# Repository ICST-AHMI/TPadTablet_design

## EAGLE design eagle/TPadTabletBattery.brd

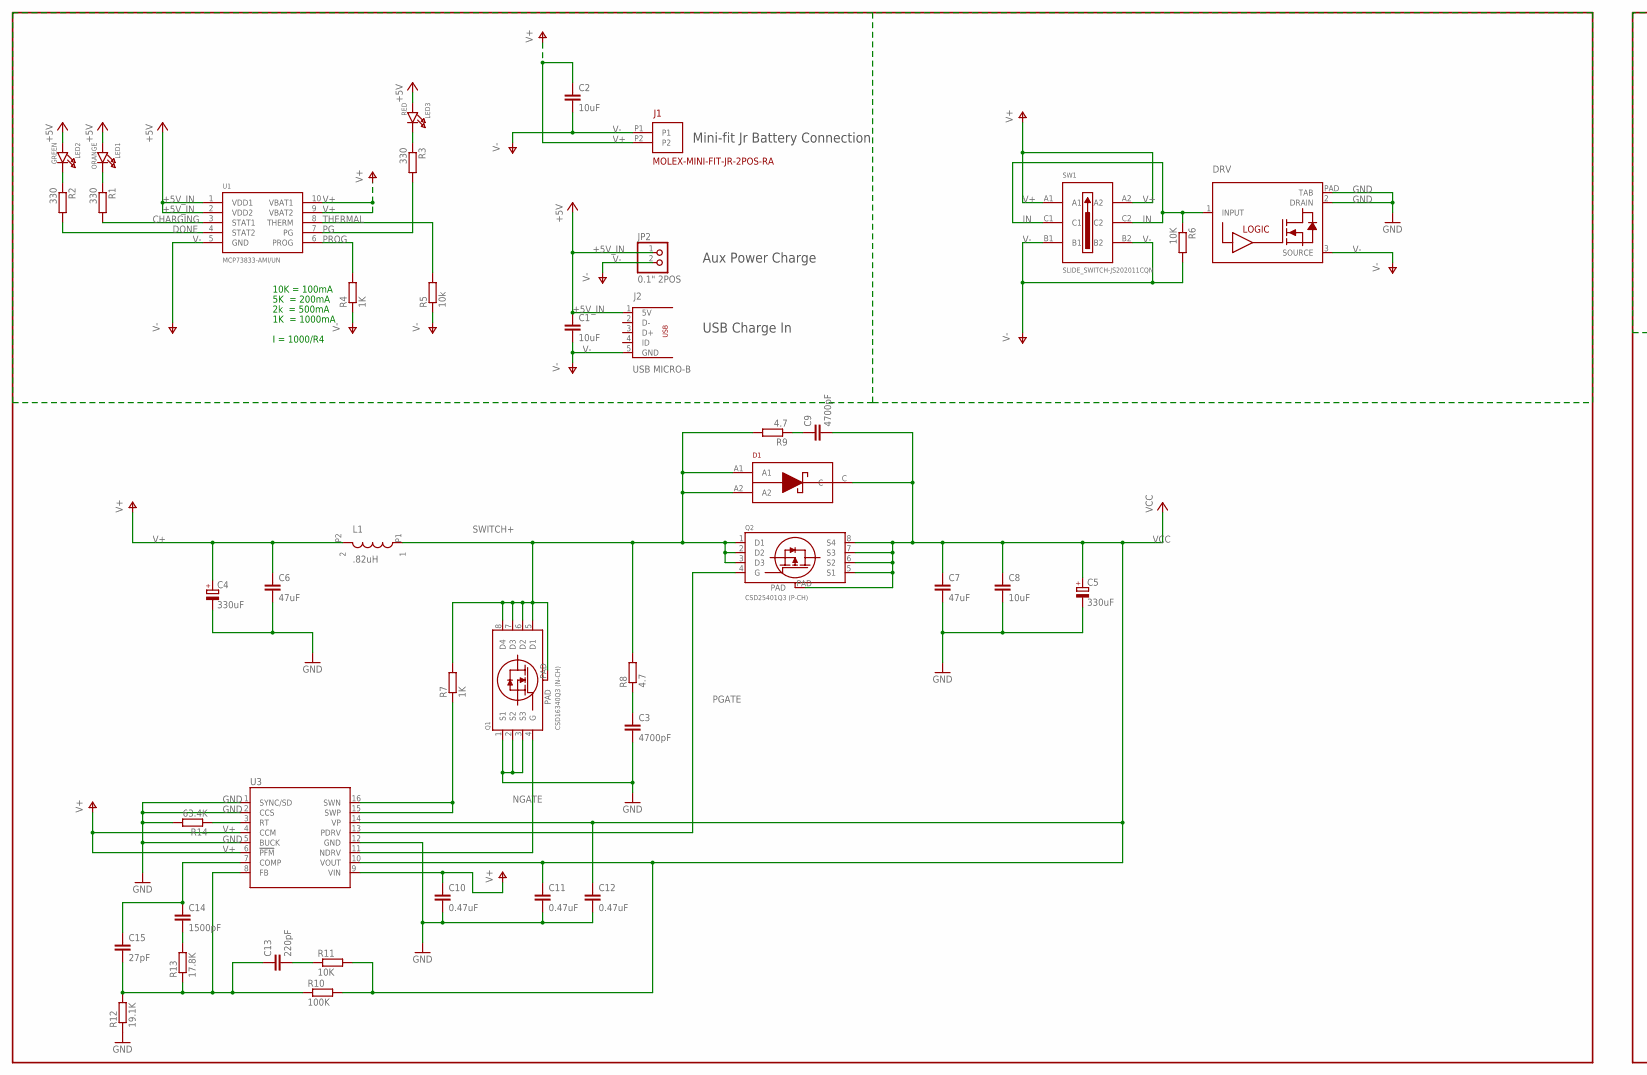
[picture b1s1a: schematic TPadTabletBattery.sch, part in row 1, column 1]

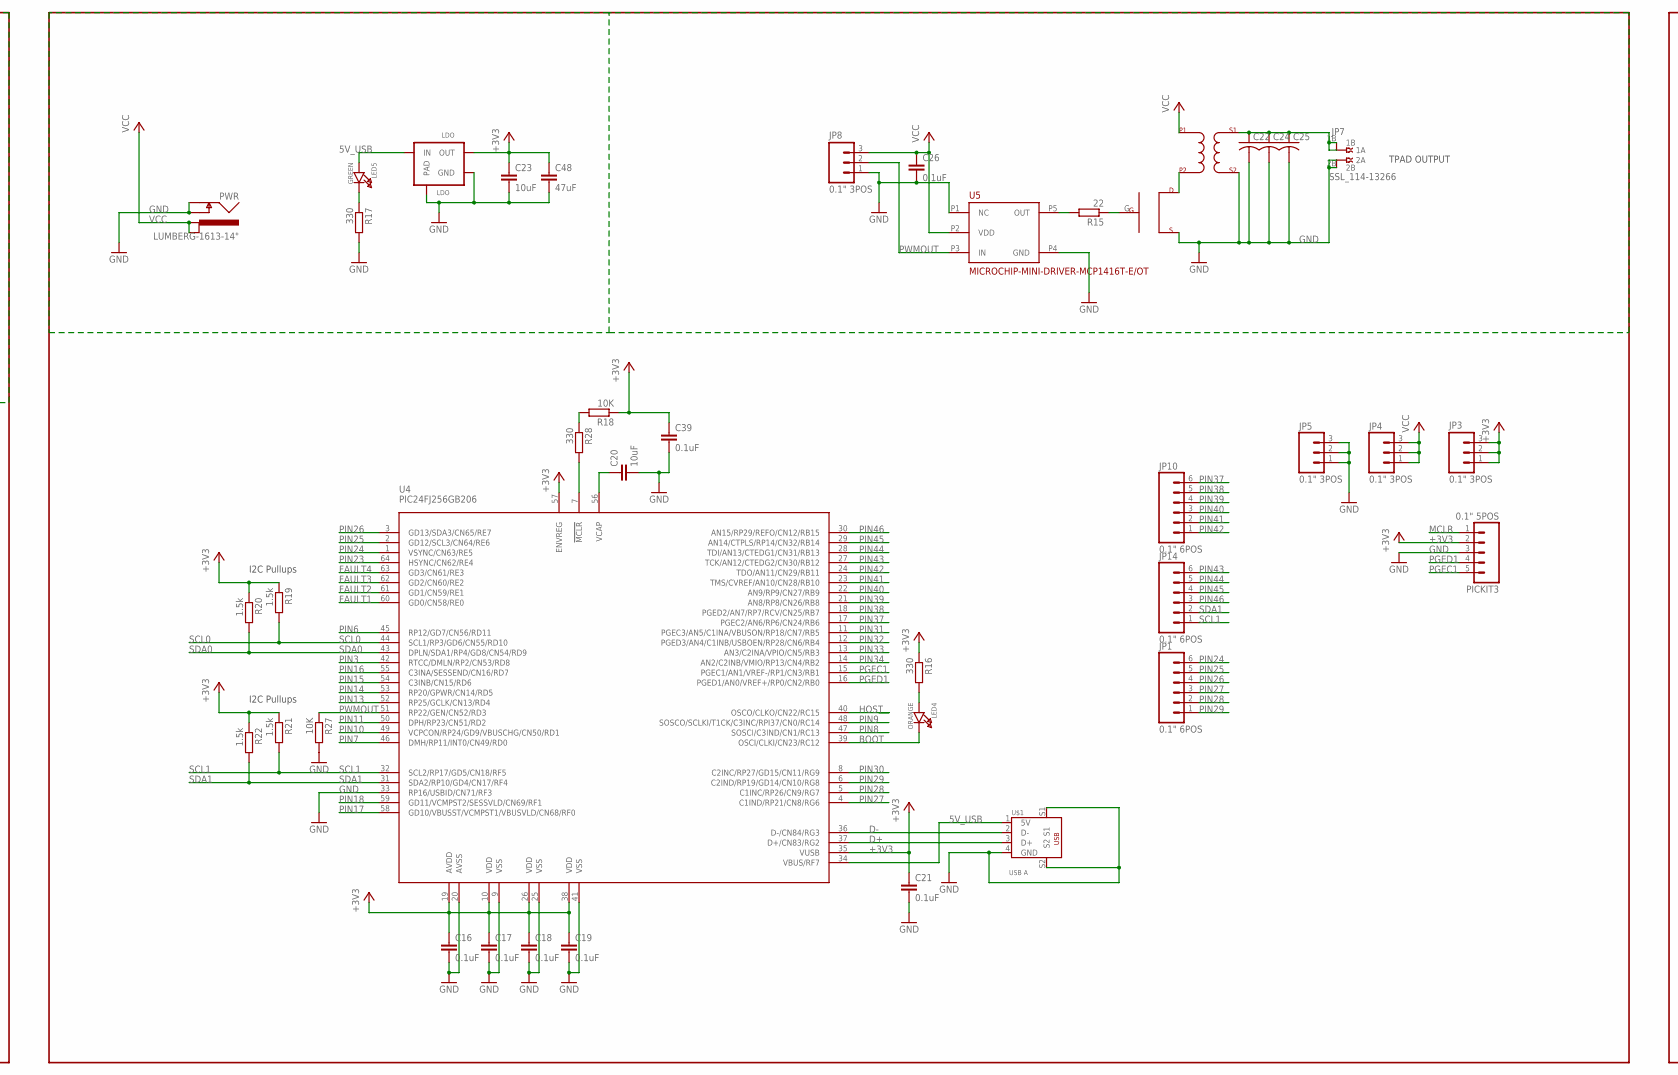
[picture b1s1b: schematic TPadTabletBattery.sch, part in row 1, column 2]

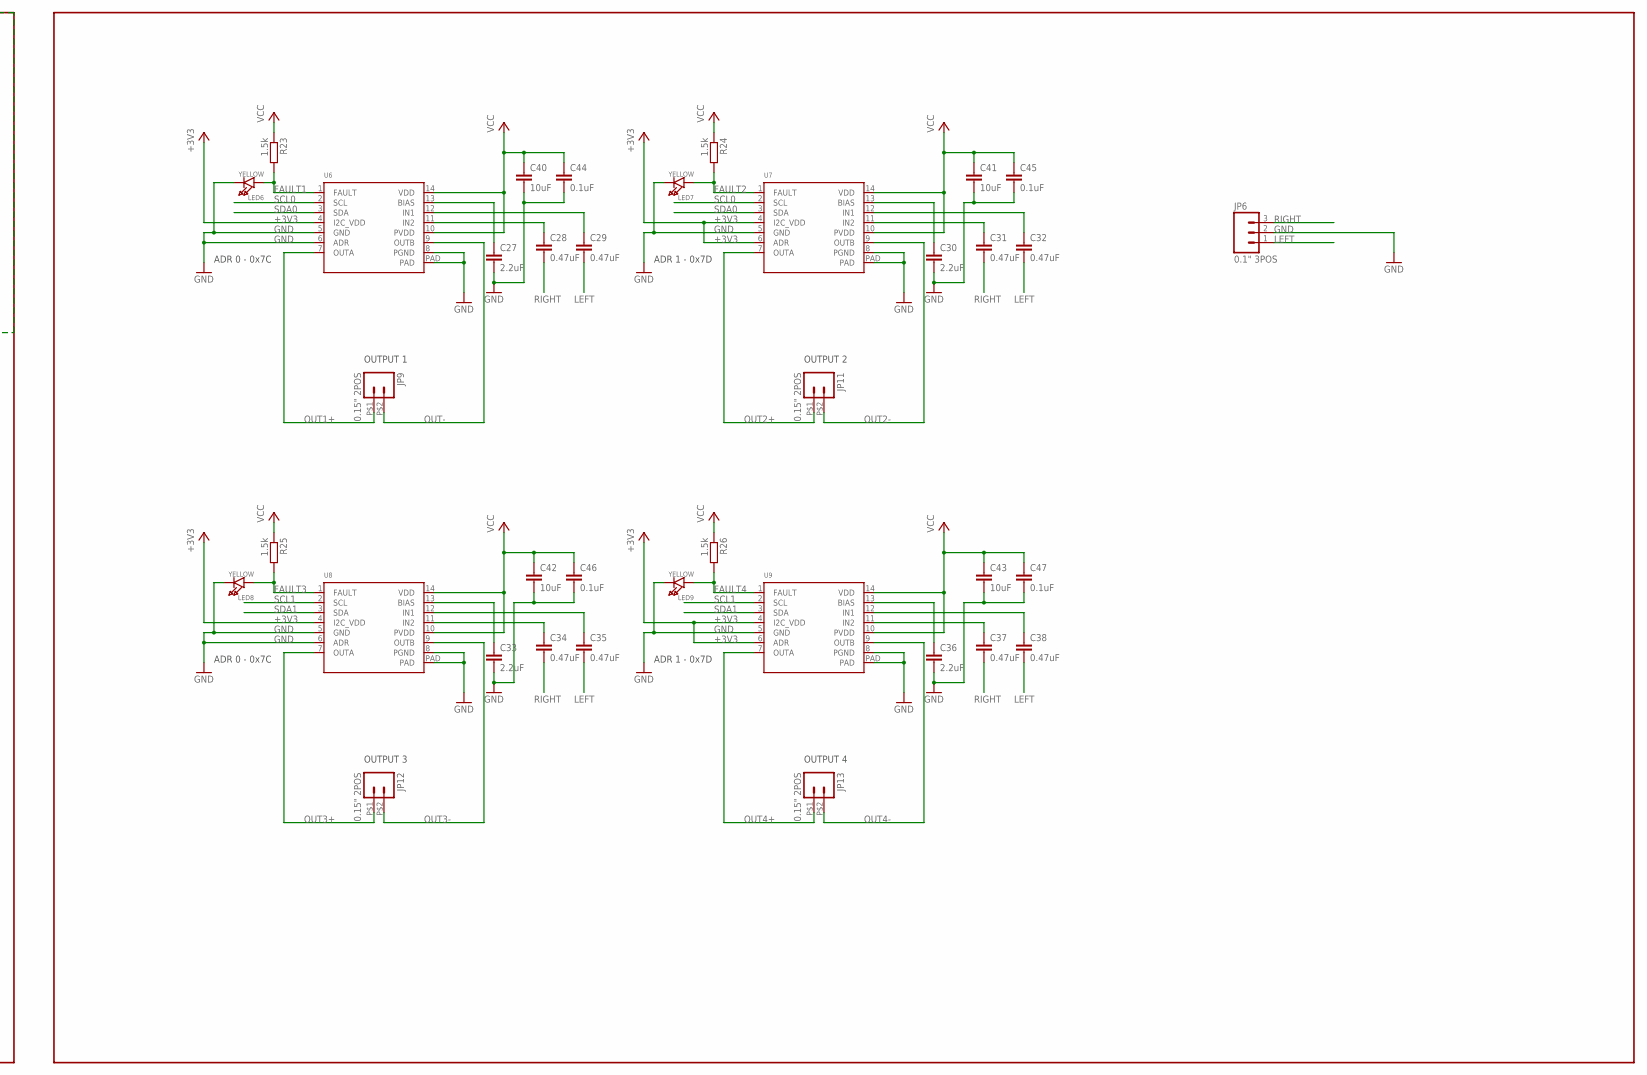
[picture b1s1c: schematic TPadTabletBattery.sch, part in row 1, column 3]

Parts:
C1, C2, C8, C20, C23, C40, C41, C42, C43: 10uF; C0805
C3, C9: 4700pF; C0603
C4, C5: 330uF; C/6032-28R
C6, C7, C48: 47uF; C1210
C10, C11, C12, C28, C29, C31, C32, C34, C35, C37, C38: 0.47uF; C0603
C13: 220pF; C0603
C14: 1500pF; C0603
C15: 27pF; C0603
C16, C17, C18, C19, C21, C26, C39, C44, C45, C46, C47: 0.1uF; C0603
C22, C24, C25: C-US050-035X075; C050-035X075
C27, C30, C33, C36: 2.2uF; C0603
D1: POWER-DIODE_PDS835L
DRV: VLN5050; SOT-223
J1: MOLEX-MINI-FIT-JR-2POS-RA
J2: USB MICRO-B; USB-MICROB_SMD
JP1, JP10, JP14: 0.1" 6POS; 1X06
JP2: 0.1" 2POS; MICROBUILDER_1X02_ROUND
JP3, JP4, JP5, JP6, JP8: 0.1" 3POS; 1X03
JP7: SSL_114-13266
JP9, JP11, JP12, JP13: 0.15" 2POS; 1X02_BIG
L1: .82uH; .82UH_INDUCTOR-IHLP3232DZERR82M01
LDO: LDO; SOT-223
LED1, LED4: ORANGE; MICROBUILDER_CHIPLED_0603
LED2, LED5: GREEN; MICROBUILDER_CHIPLED_0603
LED3: RED; MICROBUILDER_CHIPLED_0603
LED6, LED7, LED8, LED9: YELLOW; MICROBUILDER_CHIPLED_0603
PICKIT3: 0.1" 5POS; 1X05
PWR: LUMBERG-1613-14"; LUMBERG-1613_14
Q1: CSD16340Q3; CSDXXXXQ3
Q2: CSD25401Q3; CSDXXXXQ3
Q3: STP27N3LH5; TPAD_TO220
R1, R2, R3, R16, R17, R28: 330; R0603
R4: 1K; R0805
R5: 10k; R0805
R6, R11, R18, R27: 10K; R0603
R7: 1K; R0603
R8, R9: 4.7; R0603
R10: 100K; R0603
R12: 19.1K; R0603
R13: 17.8K; R0603
R14: 63.4K; R0603
R15: 22; R0603
R19, R20, R21, R22, R23, R24, R25, R26: 1.5k; R0603
SW1: SLIDE_SWITCH-JS202011CQN
U1: MCP73833-AMI/UN; MICROBUILDER_MSOP10
U3: TPS43000; TSSOP16
U4: PIC24FJ256GB206; PIC24FXXX_TQFP64
U5: MICROCHIP-MINI-DRIVER-MCP1416T-E/OT
U6, U7, U8, U9: LM48100Q; LM48100
U$1: USB A; USB-A_SOCKET-THT
U$4: TRANSFORMER

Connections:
5V_USB: LDO.1 (IN), LED5.A, U4.34 (VBUS/RF7), U$1.1 (5V)
+3V3: C16.1, C17.1, C18.1, C19.1, C21.1, C23.1, C39.1, C48.1, JP3.1, JP3.2, JP3.3, LDO.3 (OUT), PICKIT3.2, R16.1, R18.1, R19.1, R20.1, R21.1, R22.1, U4.10 (VDD), U4.19 (AVDD), U4.26 (VDD), U4.35 (VUSB), U4.38 (VDD), U4.57 (ENVREG), U6.4 (I2C_VDD), U7.4 (I2C_VDD), U7.6 (ADR), U8.4 (I2C_VDD), U9.4 (I2C_VDD), U9.6 (ADR)
+5V_IN: C1.1, J2.1 (5V), JP2.1, LED1.A, LED2.A, LED3.A, U1.1 (VDD1), U1.2 (VDD2)
BOOT: LED4.C, U4.39 (OSCI/CLKI/CN23/RC12)
CHARGING: R1.2, U1.3 (STAT1)
D+: U4.37 (D+/CN83/RG2), U$1.3 (D+)
D-: U4.36 (D-/CN84/RG3), U$1.2 (D-)
DONE: R2.2, U1.4 (STAT2)
FAULT1: LED6.A, R23.2, U4.60 (GD0/CN58/RE0), U6.1 (FAULT)
FAULT2: LED7.A, R24.2, U4.61 (GD1/CN59/RE1), U7.1 (FAULT)
FAULT3: LED8.A, R25.2, U4.62 (GD2/CN60/RE2), U8.1 (FAULT)
FAULT4: LED9.A, R26.2, U4.63 (GD3/CN61/RE3), U9.1 (FAULT)
GND: C3.2, C4.-, C5.-, C6.2, C7.2, C8.2, C10.2, C11.2, C12.2, C16.2, C17.2, C18.2, C19.2, C20.2, C21.2, C22.2, C23.2, C24.2, C25.2, C26.2, C27.2, C30.2, C33.2, C36.2, C39.2, C40.2, C41.2, C42.2, C43.2, C44.2, C45.2, C46.2, C47.2, C48.2, DRV.2 (DRAIN), DRV.PAD (TAB), JP5.1, JP5.2, JP5.3, JP6.2, JP7.2A, JP7.2B, JP8.1, LDO.2 (GND), LDO.PAD, LED6.C, LED7.C, LED8.C, LED9.C, PICKIT3.3, PWR.1 (GND), PWR.2 (GND_INS), Q1.1 (S1), Q1.2 (S2), Q1.3 (S3), Q3.S, R12.1, R14.2, R17.2, R27.2, U3.1 (SYNC/SD), U3.2 (CCS), U3.5 (BUCK), U3.12 (GND), U4.9 (VSS), U4.20 (AVSS), U4.25 (VSS), U4.33 (RP16/USBID/CN71/RF3), U4.41 (VSS), U5.P1 (NC), U5.P4 (GND), U6.5 (GND), U6.6 (ADR), U6.8 (PGND), U6.PAD, U7.5 (GND), U7.8 (PGND), U7.PAD, U8.5 (GND), U8.6 (ADR), U8.8 (PGND), U8.PAD, U9.5 (GND), U9.8 (PGND), U9.PAD, U$1.4 (GND), U$1.S1, U$1.S2, U$4.S2
HOST: U4.40 (OSCO/CLKO/CN22/RC15)
IN: DRV.1 (INPUT), R6.1, SW1.C1, SW1.C2
LEFT: C29.2, C32.2, C35.2, C38.2, JP6.1
MCLR: PICKIT3.1, R18.2, R28.1
unnamed: R7.1, U3.15 (SWP), U3.16 (SWN)
unnamed: LED2.C, R2.1
unnamed: LED1.C, R1.1
unnamed: LED3.C, R3.1
unnamed: R28.2, U4.7 (!MCLR)
unnamed: C9.1, R9.1
unnamed: C13.1, C15.2, R10.1, R12.2, R13.1, U3.8 (FB)
unnamed: C14.1, C15.1, U3.7 (COMP)
unnamed: C3.1, R8.1
unnamed: C20.1, U4.56 (VCAP)
unnamed: R14.1, U3.3 (RT)
unnamed: C14.2, R13.2
unnamed: LED4.A, R16.2
unnamed: C13.2, R11.1
unnamed: Q3.D, U$4.P2
unnamed: R15.2, U5.P5 (OUT)
unnamed: C22.1, C24.1, C25.1, JP7.1A, JP7.1B, U$4.S1
unnamed: LED5.C, R17.1
unnamed: Q3.G, R15.1
unnamed: C27.1, U6.13 (BIAS)
unnamed: C29.1, U6.12 (IN1)
unnamed: C28.1, U6.11 (IN2)
unnamed: C30.1, U7.13 (BIAS)
unnamed: C32.1, U7.12 (IN1)
unnamed: C31.1, U7.11 (IN2)
unnamed: C33.1, U8.13 (BIAS)
unnamed: C35.1, U8.12 (IN1)
unnamed: C34.1, U8.11 (IN2)
unnamed: C36.1, U9.13 (BIAS)
unnamed: C38.1, U9.12 (IN1)
unnamed: C37.1, U9.11 (IN2)
NGATE: Q1.4 (G), U3.11 (NDRV)
OUT1+: JP9.P$1 (1), U6.7 (OUTA)
OUT2+: JP11.P$1 (1), U7.7 (OUTA)
OUT2-: JP11.P$2 (2), U7.9 (OUTB)
OUT3+: JP12.P$1 (1), U8.7 (OUTA)
OUT3-: JP12.P$2 (2), U8.9 (OUTB)
OUT4+: JP13.P$1 (1), U9.7 (OUTA)
OUT4-: JP13.P$2 (2), U9.9 (OUTB)
OUT-: JP9.P$2 (2), U6.9 (OUTB)
PG: R3.2, U1.7 (PG)
PGATE: Q2.4 (G), U3.13 (PDRV)
PGEC1: PICKIT3.5, U4.15 (PGEC1/AN1/VREF-/RP1/CN3/RB1)
PGED1: PICKIT3.4, U4.16 (PGED1/AN0/VREF+/RP0/CN2/RB0)
PIN3: U4.42 (RTCC/DMLN/RP2/CN53/RD8)
PIN6: U4.45 (RP12/GD7/CN56/RD11)
PIN7: U4.46 (DMH/RP11/INT0/CN49/RD0)
PIN8: U4.47 (SOSCI/C3IND/CN1/RC13)
PIN9: U4.48 (SOSCO/SCLKI/T1CK/C3INC/RPI37/CN0/RC14)
PIN10: U4.49 (VCPCON/RP24/GD9/VBUSCHG/CN50/RD1)
PIN11: U4.50 (DPH/RP23/CN51/RD2)
PIN13: U4.52 (RP25/GCLK/CN13/RD4)
PIN14: U4.53 (RP20/GPWR/CN14/RD5)
PIN15: U4.54 (C3INB/CN15/RD6)
PIN16: U4.55 (C3INA/SESSEND/CN16/RD7)
PIN17: U4.58 (GD10/VBUSST/VCMPST1/VBUSVLD/CN68/RF0)
PIN18: U4.59 (GD11/VCMPST2/SESSVLD/CN69/RF1)
PIN23: U4.64 (HSYNC/CN62/RE4)
PIN24: JP1.6, U4.1 (VSYNC/CN63/RE5)
PIN25: JP1.5, U4.2 (GD12/SCL3/CN64/RE6)
PIN26: JP1.4, U4.3 (GD13/SDA3/CN65/RE7)
PIN27: JP1.3, U4.4 (C1IND/RP21/CN8/RG6)
PIN28: JP1.2, U4.5 (C1INC/RP26/CN9/RG7)
PIN29: JP1.1, U4.6 (C2IND/RP19/GD14/CN10/RG8)
PIN30: U4.8 (C2INC/RP27/GD15/CN11/RG9)
PIN31: U4.11 (PGEC3/AN5/C1INA/VBUSON/RP18/CN7/RB5)
PIN32: U4.12 (PGED3/AN4/C1INB/USBOEN/RP28/CN6/RB4)
PIN33: U4.13 (AN3/C2INA/VPIO/CN5/RB3)
PIN34: U4.14 (AN2/C2INB/VMIO/RP13/CN4/RB2)
PIN37: JP10.6, U4.17 (PGEC2/AN6/RP6/CN24/RB6)
PIN38: JP10.5, U4.18 (PGED2/AN7/RP7/RCV/CN25/RB7)
PIN39: JP10.4, U4.21 (AN8/RP8/CN26/RB8)
PIN40: JP10.3, U4.22 (AN9/RP9/CN27/RB9)
PIN41: JP10.2, U4.23 (TMS/CVREF/AN10/CN28/RB10)
PIN42: JP10.1, U4.24 (TDO/AN11/CN29/RB11)
PIN43: JP14.6, U4.27 (TCK/AN12/CTEDG2/CN30/RB12)
PIN44: JP14.5, U4.28 (TDI/AN13/CTEDG1/CN31/RB13)
PIN45: JP14.4, U4.29 (AN14/CTPLS/RP14/CN32/RB14)
PIN46: JP14.3, U4.30 (AN15/RP29/REFO/CN12/RB15)
PROG: R4.2, U1.6 (PROG)
PWMOUT: JP8.2, R27.1, U4.51 (RP22/GEN/CN52/RD3), U5.P3 (IN)
RIGHT: C28.2, C31.2, C34.2, C37.2, JP6.3
SCL0: R19.2, U4.44 (SCL1/RP3/GD6/CN55/RD10), U6.2 (SCL), U7.2 (SCL)
SCL1: JP14.1, R21.2, U4.32 (SCL2/RP17/GD5/CN18/RF5), U8.2 (SCL), U9.2 (SCL)
SDA0: R20.2, U4.43 (DPLN/SDA1/RP4/GD8/CN54/RD9), U6.3 (SDA), U7.3 (SDA)
SDA1: JP14.2, R22.2, U4.31 (SDA2/RP10/GD4/CN17/RF4), U8.3 (SDA), U9.3 (SDA)
SWITCH+: D1.A1, D1.A2, L1.P1 (1), Q1.5 (D1), Q1.6 (D2), Q1.7 (D3), Q1.8 (D4), Q1.PAD, Q2.1 (D1), Q2.2 (D2), Q2.3 (D3), R7.2, R8.2, R9.2
THERMAL: R5.2, U1.8 (THERM)
V+: C2.1, C4.+, C6.1, C10.1, J1.P2, L1.P2 (2), SW1.A1, SW1.A2, U1.9 (VBAT2), U1.10 (VBAT1), U3.4 (CCM), U3.6 (!PFM), U3.9 (VIN)
V-: C1.2, C2.2, DRV.3 (SOURCE), J1.P1, J2.5 (GND), JP2.2, R4.1, R5.1, R6.2, SW1.B1, SW1.B2, U1.5 (GND)
VCC: C5.+, C7.1, C8.1, C9.2, C11.1, C12.1, C26.1, C40.1, C41.1, C42.1, C43.1, C44.1, C45.1, C46.1, C47.1, D1.C, JP4.1, JP4.2, JP4.3, JP8.3, PWR.3 (PWR_1), PWR.4 (PWR_2), Q2.5 (S1), Q2.6 (S2), Q2.7 (S3), Q2.8 (S4), Q2.PAD, R10.2, R11.2, R23.1, R24.1, R25.1, R26.1, U3.10 (VOUT), U3.14 (VP), U5.P2 (VDD), U6.10 (PVDD), U6.14 (VDD), U7.10 (PVDD), U7.14 (VDD), U8.10 (PVDD), U8.14 (VDD), U9.10 (PVDD), U9.14 (VDD), U$4.P1

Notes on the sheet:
10K = 100mA
5K = 200mA
2k = 500mA
1K = 1000mA
I = 1000/R4
Mini-fit Jr Battery Connection
USB Charge In
Aux Power Charge
ADR 0 - 0x7C
I2C Pullups
OUTPUT 1
TPAD OUTPUT
OUTPUT 2
ADR 1 - 0x7D
OUTPUT 3
OUTPUT 4

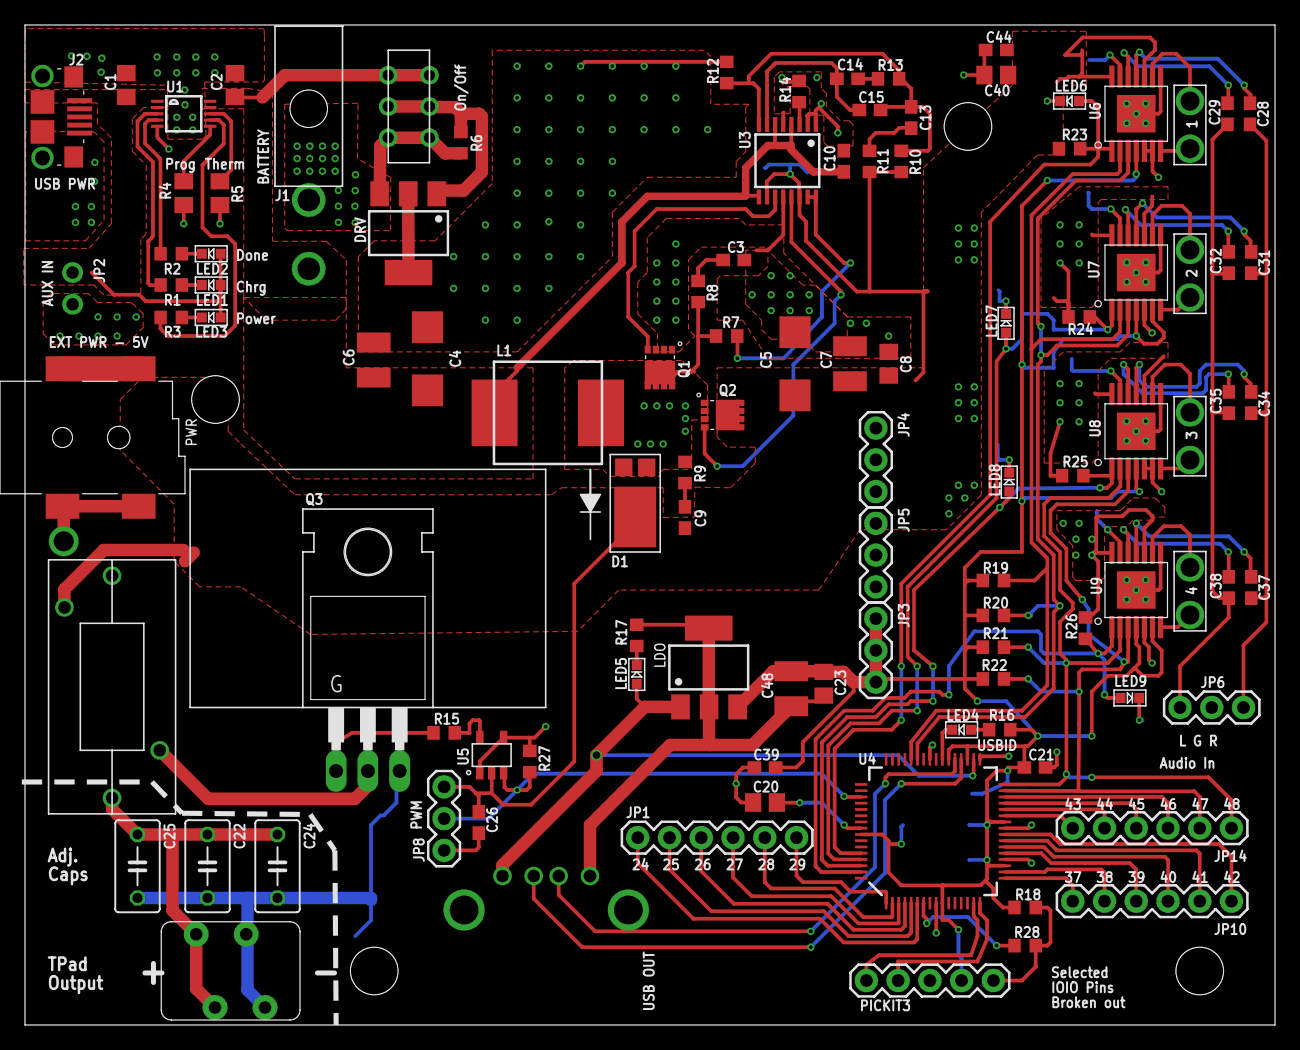
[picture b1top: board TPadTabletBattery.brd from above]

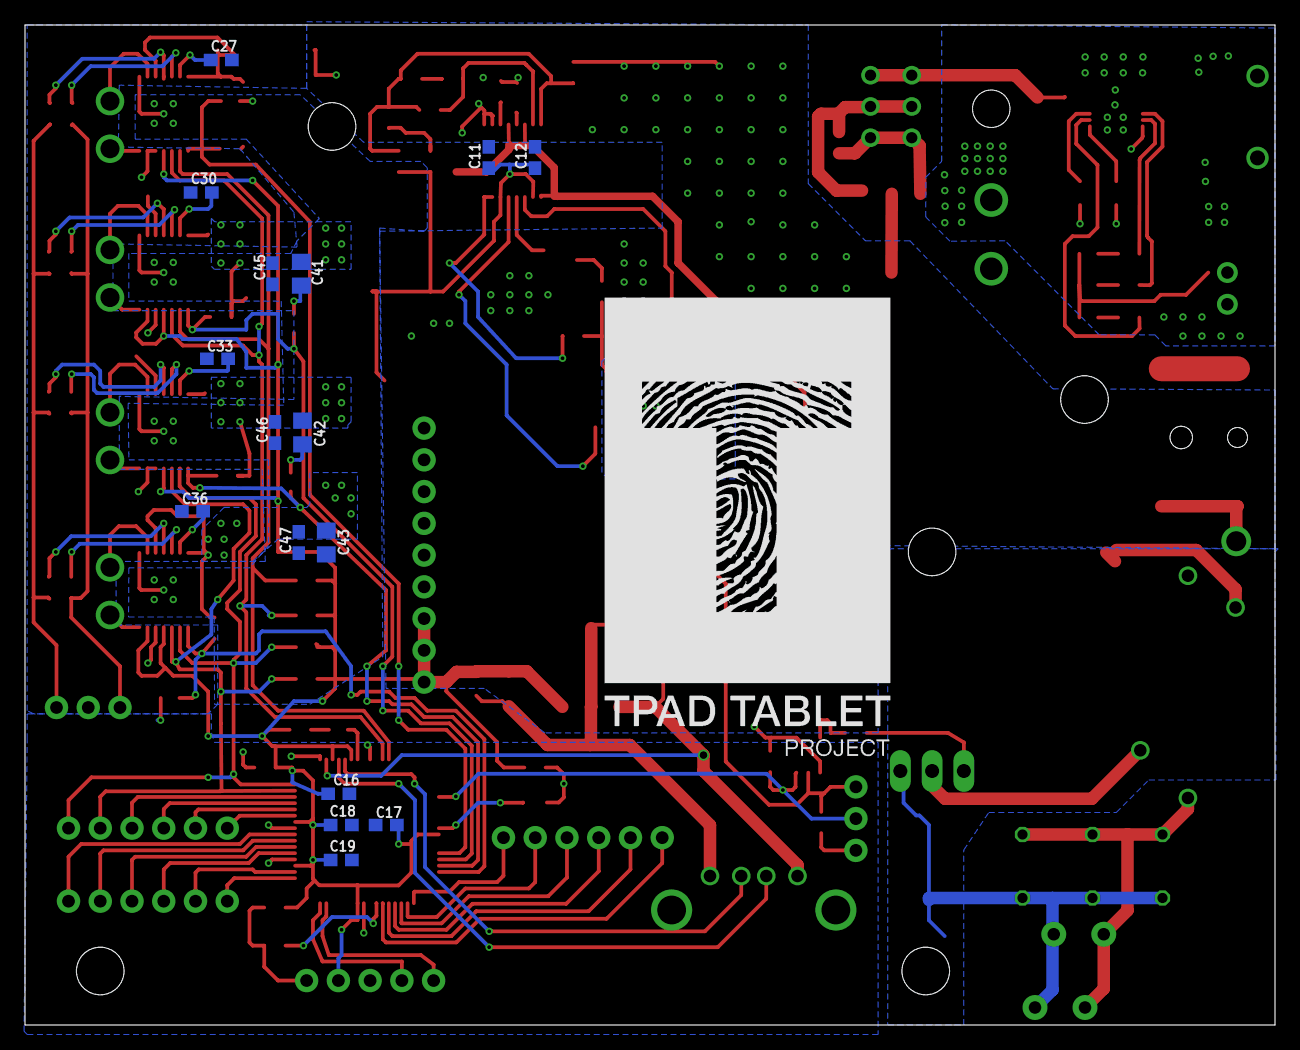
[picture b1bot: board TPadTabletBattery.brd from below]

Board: 2 copper layers, 100.0 x 80.0 mm, 122 parts (17 on the bottom side), 88 nets.

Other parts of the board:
LOGO: TPADTABLETPROJECT

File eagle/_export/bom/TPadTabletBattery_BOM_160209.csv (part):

"BILL OF MATERIAL FROM TEST_WIDERSTAENDE_AUS_RCL.SCH, 29 PARTS, GROUPED BY VALUES, AS OF 05.10.2010 16:00:00"
"Part","Value","Device","Package","Description","Description2","Qty","Place_YES/NO","Povided_by_customer_YES/NO","Distributor","Ordernumber","Weblink","Remarks_customer","Unit_price","Total_price","REMARKS_BETA","OPTION1","OPTION2","OPTION3",
"C1, C2, C8, C20, C23, C40, C41, C42, C43","10uF","C-EUC0805","C0805","CAPACITOR, European symbol","Capacitor, 0805, 10uF, 16V","9"," "," ","Beta","6911161P","http://uk.rs-online.com/web/search/searchBrowseAction.html?m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"," "," "," "," "," "," "," "
"C3, C9","4700pF","C-EUC0603","C0603","CAPACITOR, European symbol"," ","2"," "," "," "," "," "," "," "," "," "," "," "," "
"C4, C5","330uF","CPOL-EUC/6032-28R","C/6032-28R","POLARIZED CAPACITOR, European symbol"," ","2"," "," "," "," "," "," "," "," "," "," "," "," "
"C6, C7, C48","47uF","C-EUC1210","C1210","CAPACITOR, European symbol"," ","3"," "," "," "," "," "," "," "," "," "," "," "," "
"C10, C11, C12, C28, C29, C31, C32, C34, C35, C37, C38","0.47uF","C-EUC0603","C0603","CAPACITOR, European symbol"," ","11"," "," "," "," "," "," "," "," "," "," "," "," "
"C13","220pF","C-EUC0603","C0603","CAPACITOR, European symbol"," ","1"," "," "," "," "," "," "," "," "," "," "," "," "
"C14","1500pF","C-EUC0603","C0603","CAPACITOR, European symbol"," ","1"," "," "," "," "," "," "," "," "," "," "," "," "
"C15","27pF","C-EUC0603","C0603","CAPACITOR, European symbol"," ","1"," "," "," "," "," "," "," "," "," "," "," "," "
"C16, C17, C18, C19, C21, C26, C39, C44, C45, C46, C47","0.1uF","C-EUC0603","C0603","CAPACITOR, European symbol"," ","11"," "," "," "," "," "," "," "," "," "," "," "," "
"C22, C24, C25"," ","C-US050-035X075","C050-035X075","CAPACITOR, American symbol"," ","3"," "," "," "," "," "," "," "," "," "," "," "," "
"C27, C30, C33, C36","2.2uF","C-EUC0603","C0603","CAPACITOR, European symbol"," ","4"," "," "," "," "," "," "," "," "," "," "," "," "
"D1"," ","POWER-DIODE_PDS835L","POWER-DIODE_PDS835L"," ","Description2","1","Place_YES/NO","Povided_by_customer_YES/NO","Distributor","Ordernumber","Weblink","Remarks_customer","Unit_price","Total_price","REMARKS_BETA","OPTION1","OPTION2","OPTION3"
"DRV"," ","VLN5050","SOT-223"," ","Description2","1","Place_YES/NO","Povided_by_customer_YES/NO","Distributor","Ordernumber","Weblink","Remarks_customer","Unit_price","Total_price","REMARKS_BETA","OPTION1","OPTION2","OPTION3"
"J1","MOLEX-MINI-FIT-JR-2POS-RA","MOLEX-MINI-FIT-JR-2POS-RA","MOLEX-MINI-FIT-JR-2POS-RA"," "," ","1"," "," "," "," "," "," "," "," "," "," "," "," "
"J2","USB MICRO-B","USB_MICROAMPHENOL_10118193-0001LFMICRO-B","USB-MICROB_SMD"," "," ","1"," "," "," "," "," "," "," "," "," "," "," "," "
"JP1, JP10, JP14","0.1" 6POS","M06SIP","1X06","Header 6"," ","3"," "," "," "," "," "," "," "," "," "," "," "," "
"JP2","0.1" 2POS","MICROBUILDER_HEADER-1X2ROUND","MICROBUILDER_1X02_ROUND","PIN HEADER"," ","1"," "," "," "," "," "," "," "," "," "," "," "," "
"JP3, JP4, JP5, JP6, JP8","0.1" 3POS","M03PTH","1X03","Header 3"," ","5"," "," "," "," "," "," "," "," "," "," "," "," "
"JP7, JP9, JP11, JP12, JP13","0.15" 2POS","M02PTH2","1X02_BIG","Header 2"," ","5"," "," "," "," "," "," "," "," "," "," "," "," "
"L1",".82uH",".82UH_INDUCTOR-IHLP3232DZERR82M01",".82UH_INDUCTOR-IHLP3232DZERR82M01"," "," ","1"," "," "," "," "," "," "," "," "," "," "," "," "
"LDO","LDO","LDO","SOT-223"," "," ","1"," "," "," "," "," "," "," "," "," "," "," "," "
"LED1, LED4","ORANGE","MICROBUILDER_LED0603","MICROBUILDER_CHIPLED_0603","LED"," ","2"," "," "," "," "," "," "," "," "," "," "," "," "
"LED2, LED5","GREEN","MICROBUILDER_LED0603","MICROBUILDER_CHIPLED_0603","LED"," ","2"," "," "," "," "," "," "," "," "," "," "," "," "
"LED3","RED","MICROBUILDER_LED0603","MICROBUILDER_CHIPLED_0603","LED"," ","1"," "," "," "," "," "," "," "," "," "," "," "," "
"LED6, LED7, LED8, LED9","YELLOW","MICROBUILDER_LED0603","MICROBUILDER_CHIPLED_0603","LED"," ","4"," "," "," "," "," "," "," "," "," "," "," "," "
"PICKIT3","0.1" 5POS","M05PTH","1X05","Header 5"," ","1"," "," "," "," "," "," "," "," "," "," "," "," "
"PWR","LUMBERG-1613-14"","LUMBERG-1613-14"","LUMBERG-1613_14"," "," ","1"," "," "," "," "," "," "," "," "," "," "," "," "
"Q1","CSD16340Q3","CSD16340Q3","CSDXXXXQ3"," "," ","1"," "," "," "," "," "," "," "," "," "," "," "," "
"Q2","CSD25401Q3","CSD25401Q3","CSDXXXXQ3"," "," ","1"," "," "," "," "," "," "," "," "," "," "," "," "
"Q3","STP27N3LH5","TPAD_IRF520N","TPAD_TO220"," "," ","1"," "," "," "," "," "," "," "," "," "," "," "," "
"R1, R2, R3, R16, R17, R28","330","R-EU_R0603","R0603","RESISTOR, European symbol","RESISTOR, 0.1W, 1%","6"," "," ","Beta","6979202","http://uk.rs-online.com/web/search/searchBrowseAction.html?m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"," "," "," "," "," "," "," "
"R4","1K","R-EU_R0805","R0805","RESISTOR, European symbol","RESISTOR, 0.125W, 1%","1"," "," ","Beta","6980075","http://uk.rs-online.com/web/search/searchBrowseAction.html?m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"," "," "," "," "," "," "," "
"R5","10k","R-EU_R0805","R0805","RESISTOR, European symbol","RESISTOR, 0.125W, 1%","1"," "," ","Beta","6980154","http://uk.rs-online.com/web/search/searchBrowseAction.html?m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"," "," "," "," "," "," "," "
"R6, R11, R18, R27","10K","R-EU_R0603","R0603","RESISTOR, European symbol","RESISTOR, 0.1W, 1%","4"," "," ","Beta","6979325","http://uk.rs-online.com/web/search/searchBrowseAction.html?m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"," "," "," "," "," "," "," "
"R7","1K","R-EU_R0603","R0603","RESISTOR, European symbol","RESISTOR, 0.1W, 1%","1"," "," ","Beta","6979246","http://uk.rs-online.com/web/search/searchBrowseAction.html?m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"," "," "," "," "," "," "," "
"R8, R9","4.7","R-EU_R0603","R0603","RESISTOR, European symbol"," ","2"," "," "," "," "," "," "," "," "," "," "," "," "
"R10","100K","R-EU_R0603","R0603","RESISTOR, European symbol","RESISTOR, 0.1W, 1%","1"," "," ","Beta","697-9438","http://de.rs-online.com/web/p/products/6979438/?searchTerm=6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"," "," "," "," "," "," "," "
"R12","19.1K","R-EU_R0603","R0603","RESISTOR, European symbol"," ","1"," "," "," "," "," "," "," "," "," "," "," "," "
"R13","17.8K","R-EU_R0603","R0603","RESISTOR, European symbol"," ","1"," "," "," "," "," "," "," "," "," "," "," "," "
"R14","63.4K","R-EU_R0603","R0603","RESISTOR, European symbol"," ","1"," "," "," "," "," "," "," "," "," "," "," "," "
"R15","22","R-EU_R0603","R0603","RESISTOR, European symbol","RESISTOR, 0.1W, 1%","1"," "," ","Beta","6979113","http://uk.rs-online.com/web/search/searchBrowseAction.html?m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"," "," "," "," "," "," "," "
"R19, R20, R21, R22, R23, R24, R25, R26","1.5k","R-EU_R0603","R0603","RESISTOR, European symbol","RESISTOR, 0.1W, 1%","8"," "," ","Beta","6979261","http://uk.rs-online.com/web/search/searchBrowseAction.html?m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"," "," "," "," "," "," "," "
"SW1","SLIDE_SWITCH-JS202011CQN","SLIDE_SWITCH-JS202011CQN","SLIDE_SWITCH-JS202011CQN"," "," ","1"," "," "," "," "," "," "," "," "," "," "," "," "
"U$1","USB A","USBSOCKET-THT","USB-A_SOCKET-THT"," "," ","1"," "," "," "," "," "," "," "," "," "," "," "," "
"U$4","TRANSFORMER","TRANSFORMER","TRANSFORMER"," "," ","1"," "," "," "," "," "," "," "," "," "," "," "," "
"U1","MCP73833-AMI/UN","MICROBUILDER_MCP73833","MICROBUILDER_MSOP10","Lithium-Polymer/Lithium-Ion Battery Charger [Part No.]"," ","1"," "," "," "," "," "," "," "," "," "," "," "," "
"U3"," ","TPS43000","TSSOP16"," ","Description2","1","Place_YES/NO","Povided_by_customer_YES/NO","Distributor","Ordernumber","Weblink","Remarks_customer","Unit_price","Total_price","REMARKS_BETA","OPTION1","OPTION2","OPTION3"
"U4","PIC24FJ256GB206","PIC24FXXXDAX06","PIC24FXXX_TQFP64","PIC24FXXXDAX06"," ","1"," "," "," "," "," "," "," "," "," "," "," "," "
"U5","MICROCHIP-MINI-DRIVER-MCP1416T-E/OT","MICROCHIP-MINI-DRIVER-MCP1416T-E/OT","MICROCHIP-MINI-DRIVER-MCP1416T-E/OT"," "," ","1"," "," "," "," "," "," "," "," "," "," "," "," "
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
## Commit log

2016-03-23 added blender folder

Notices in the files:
parts and their libraries:
SparkFun-DigitalIC: Licensing: CC v3.0 Share-Alike You are welcome to use this library for commercial purposes.
